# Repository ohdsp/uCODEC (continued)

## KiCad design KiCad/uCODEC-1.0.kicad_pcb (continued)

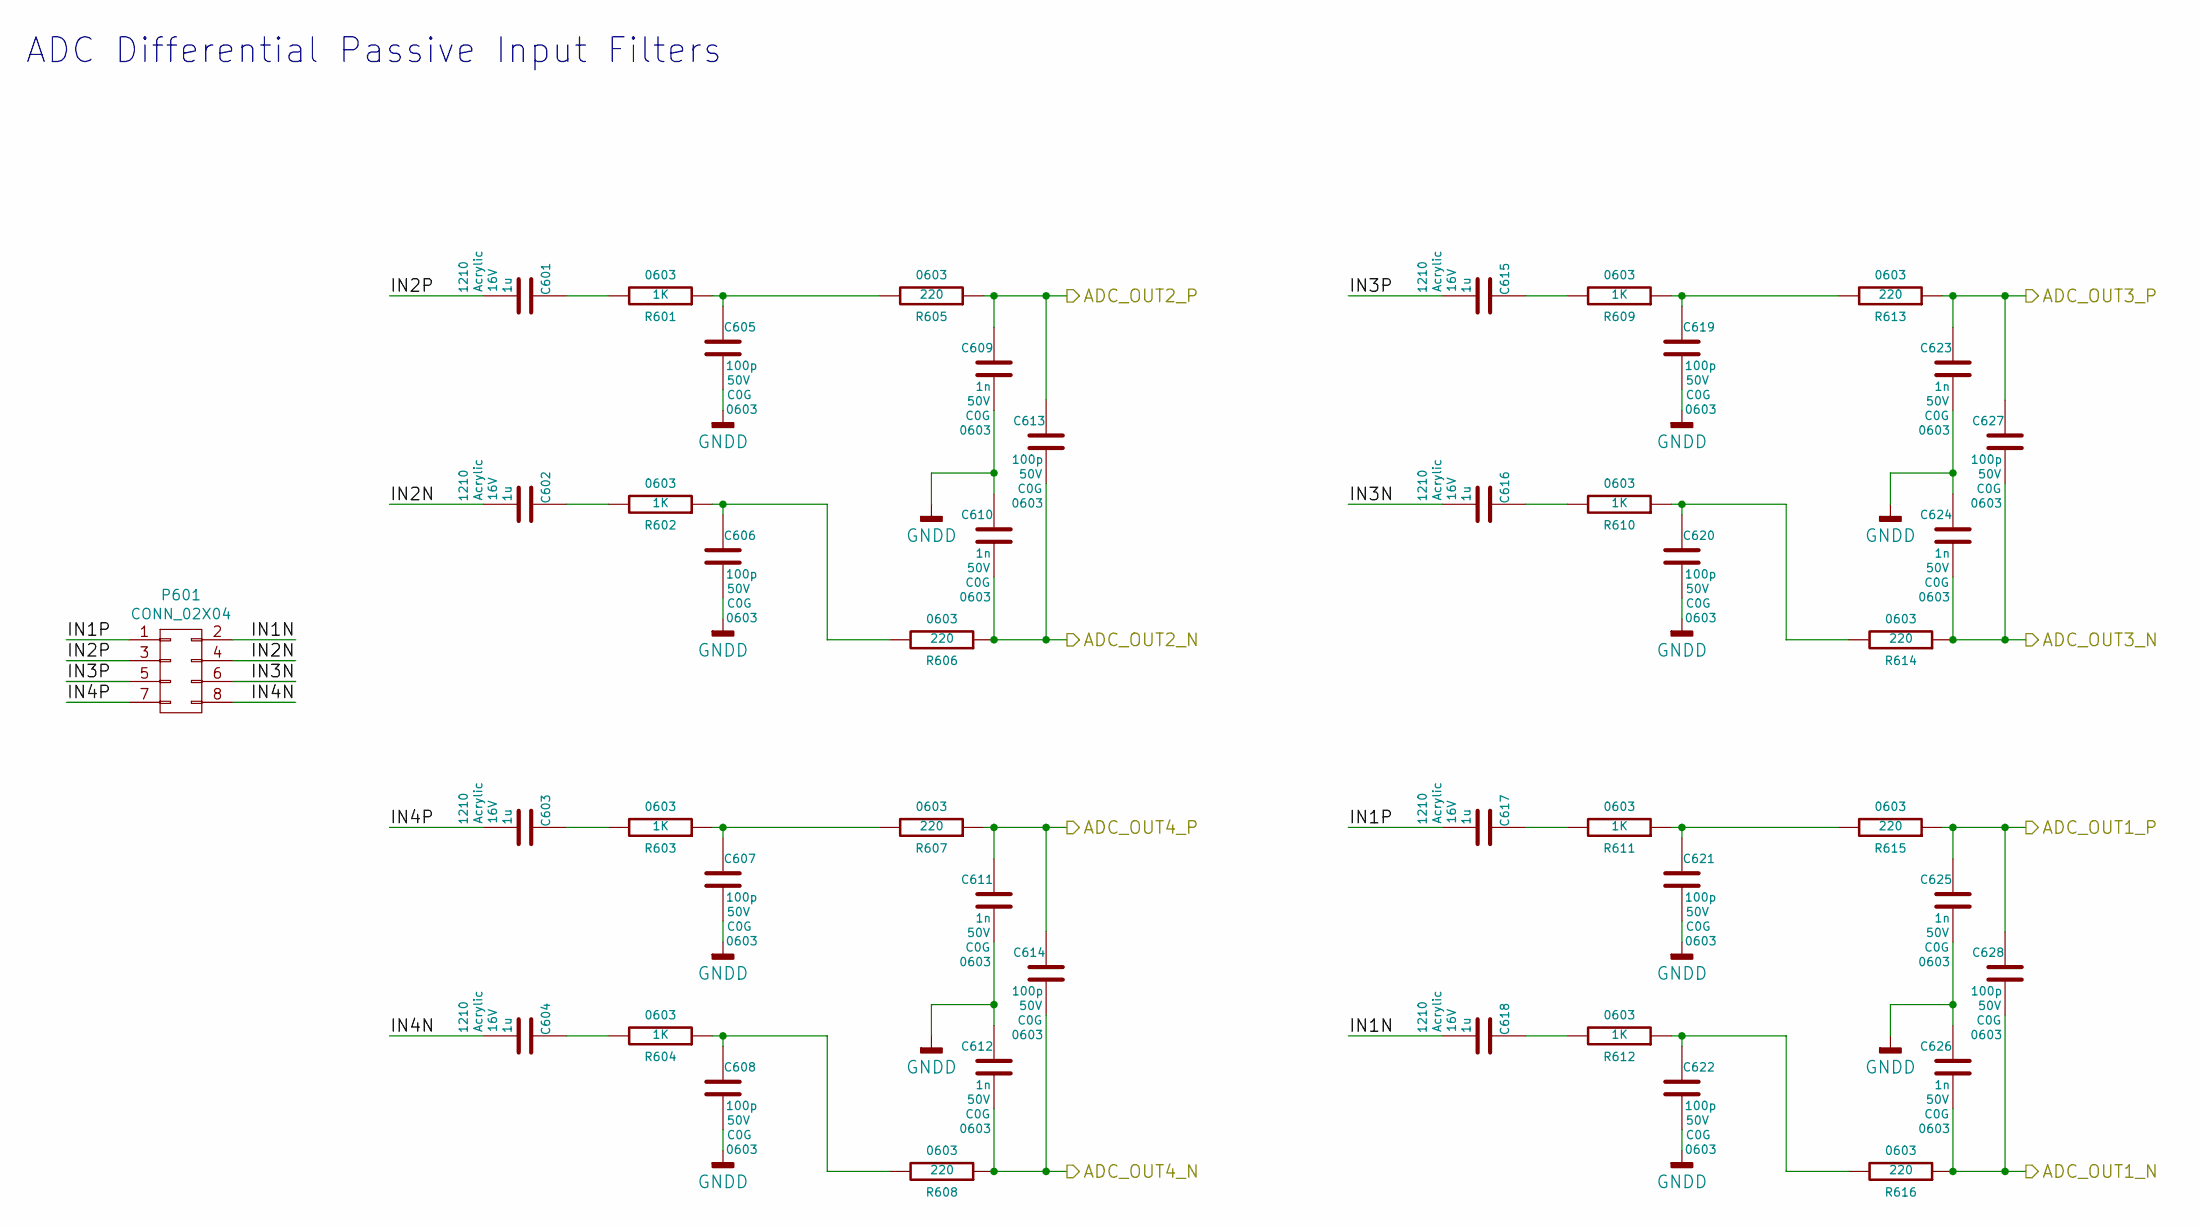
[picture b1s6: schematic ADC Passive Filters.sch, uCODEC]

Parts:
C601, C602, C604, C615, C616, C617, C618: 1u; SMD-1210; Voltage 16V; Tolerance 20%
C603, C607, C608, C609, C614, C619, C620, C621, C622, C627, C628: 100p; SMD-0603; Voltage 50V; Tolerance 5%
C605, C606, C611, C612, C623, C624, C625, C626: 1n; SMD-0603; Voltage 50V; Tolerance 5%
P601: CONN_02X04; CONN_DIL_2X04
R601, R602, R603, R604, R609, R610, R611, R612: 1K; SMD-0603; Tolerance 1%
R607, R608, R613, R614, R615, R616: 220; SMD-0603; Tolerance 1%

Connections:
/ADC2LN: C624.2, C627.2, R614.1; also elsewhere on the board
/ADC2LP: C623.1, C627.1, R613.1; also elsewhere on the board
/ADC2RN: C612.2, C614.2, R608.1; also elsewhere on the board
/ADC2RP: C611.1, C614.1, R607.1; also elsewhere on the board
/ADC Passive Filters/IN1N: C618.2, P601.2
/ADC Passive Filters/IN1P: C617.2, P601.1
/ADC Passive Filters/IN2N: C602.2, P601.4
/ADC Passive Filters/IN2P: C601.2, P601.3
/ADC Passive Filters/IN3N: C616.2, P601.6
/ADC Passive Filters/IN3P: C615.2, P601.5
/ADC Passive Filters/IN4N: C604.2, P601.8
unnamed: C601.1, R601.2
unnamed: C602.1, R602.2
unnamed: C604.1, R604.2
unnamed: C607.1, R603.1, R607.2
unnamed: C608.1, R604.1, R608.2
unnamed: C615.1, R609.2
unnamed: C616.1, R610.2
unnamed: C617.1, R611.2
unnamed: C618.1, R612.2
unnamed: C619.1, R609.1, R613.2
unnamed: C620.1, R610.1, R614.2

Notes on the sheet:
ADC Differential Passive Input Filters

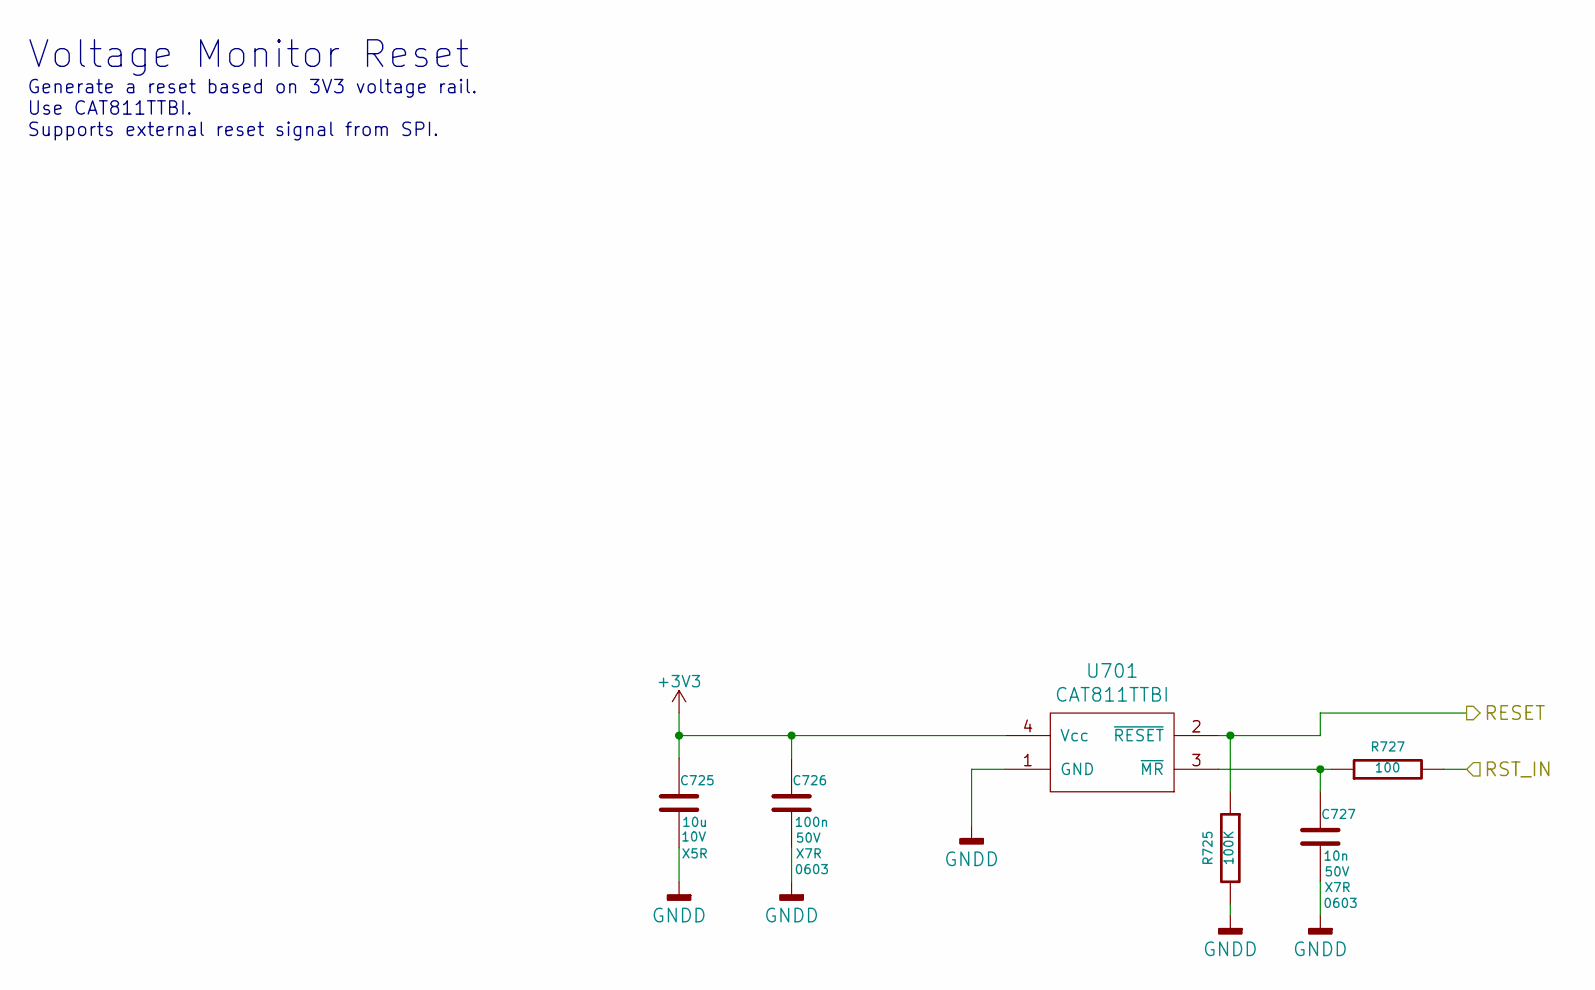
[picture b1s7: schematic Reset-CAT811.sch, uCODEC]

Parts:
C725: 10u; SMD-0603; Voltage 10V; Tolerance 20%
C726: 100n; SMD-0603; Voltage 50V; Tolerance 10%
C727: 10n; SMD-0603; Voltage 50V; Tolerance 10%
R725: 100K; SMD-0603; Tolerance 1%
R727: 100; SMD-0603; Tolerance 1%
U701: CAT811TTBI; IC-SOT143

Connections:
+3V3: C725.1, C726.1, U701.4 (Vcc); also elsewhere on the board
/CODEC_RST: R725.1, U701.2 (~RESET); also elsewhere on the board
/GLB_RESET: R727.2; also elsewhere on the board
unnamed: C727.1, R727.1, U701.3 (~MR)

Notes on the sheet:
Generate a reset based on 3V3 voltage rail. Use CAT811TTBI. Supports external reset signal from SPI.
Voltage Monitor Reset

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
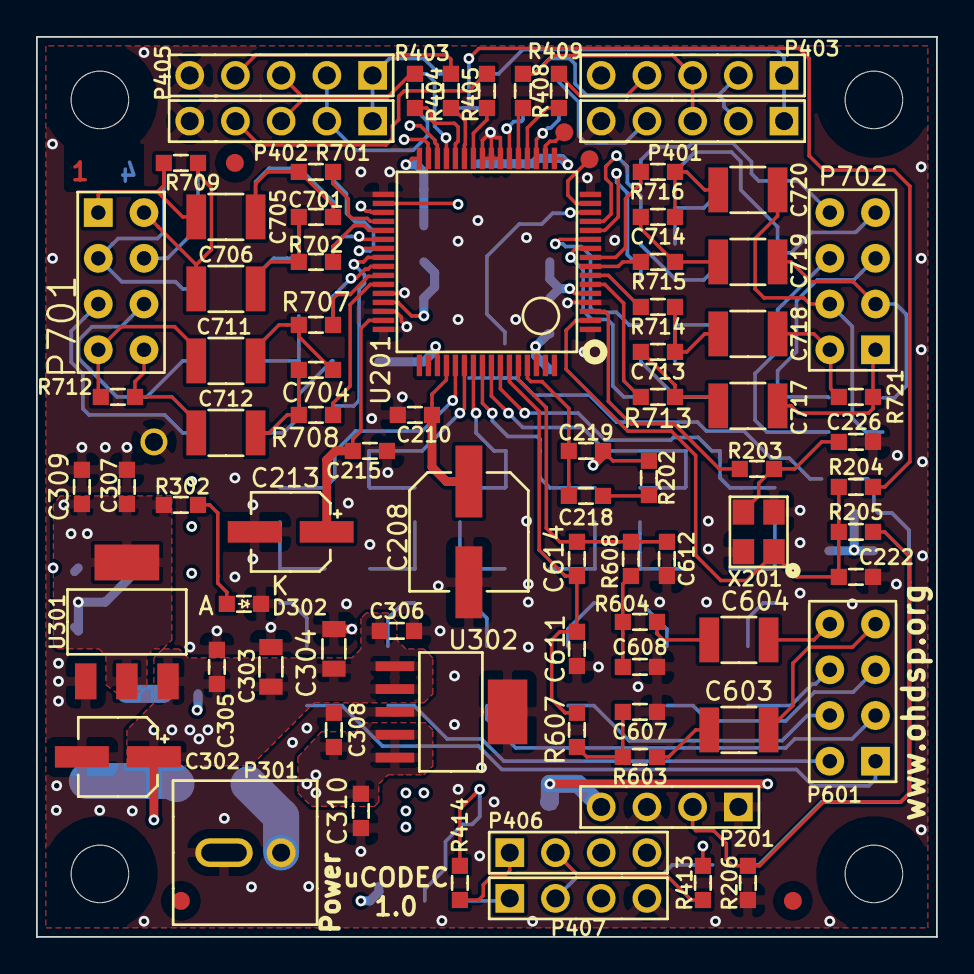
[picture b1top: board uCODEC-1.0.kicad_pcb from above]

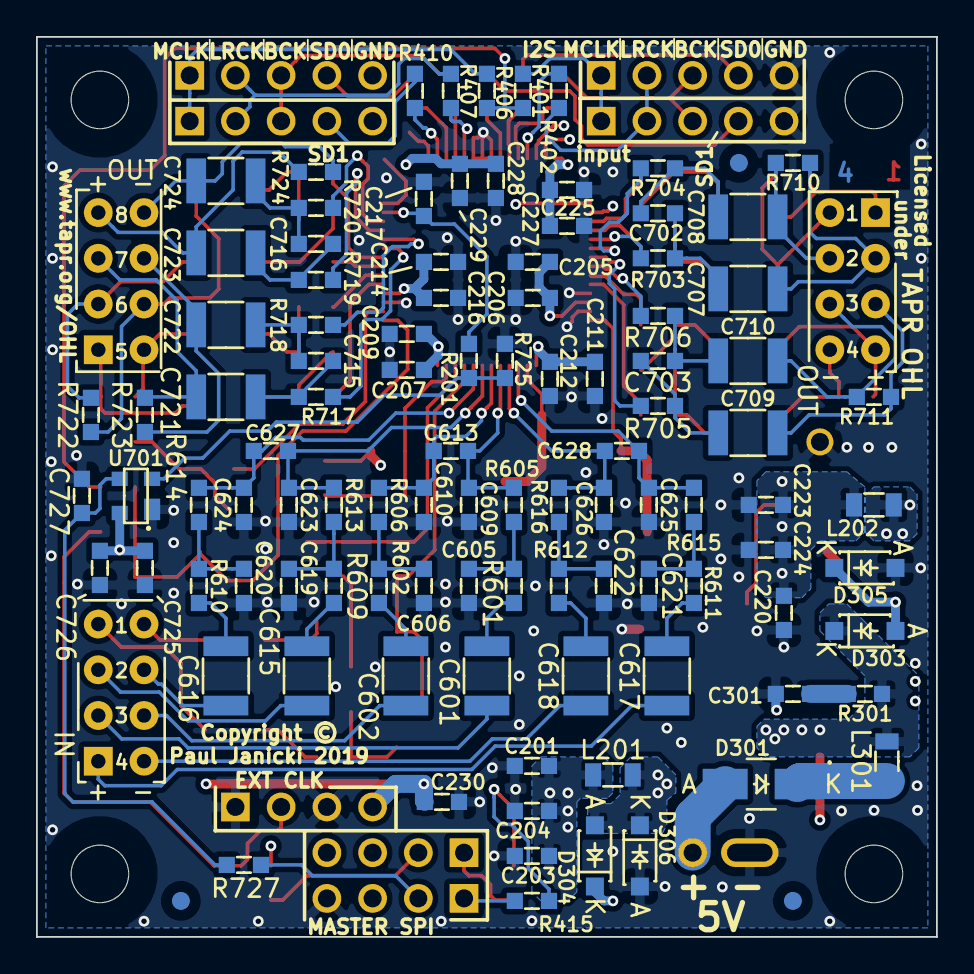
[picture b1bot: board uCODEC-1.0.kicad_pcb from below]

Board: 4 copper layers, 50.0 x 50.0 mm, 194 parts (104 on the bottom side), 130 nets.

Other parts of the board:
C610: 1n; SMD-0603
C613: 100p; SMD-0603
R605, R606: 220; SMD-0603

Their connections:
/ADC1RN: C610.2, C613.2, R606.1; also elsewhere on the board

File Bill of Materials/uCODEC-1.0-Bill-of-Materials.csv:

Reference; Quantity; Footprint; Value; Description; Size; Tolerance; Type; Voltage; Power; Current; 
C201 C220 C301 ;3;SMD-0603;100p;'Ceramic capacitor;'0603;'5%;'NP0;'50V;';';
C204 C205 C207 C210 C211 C214 C215 C224 C225 C228 C230 C305 C306 C307 C308 C726 ;16;SMD-0603;100n;'Ceramic capacitor;'0603;'10%;'X7R;'50V;';';
C206 C209 C212 C216 C217 C227 C229 C727 ;8;SMD-0603;10n;'Ceramic capacitor;'0603;'10%;'X7R;'50V;';';
C208 ;1;CAP-SMD-SIZE-D;47u;'Low impedance aluminium electrolytic capacitor - Panasonic FP, FK or Similar;';';'Case D SMD Aluminium Electrolytic;'16V;';';
C213 C302 ;2;CAP-SMD-SIZE-B;10u;'Low impedance aluminium electrolytic capacitor - Panasonic FP, FK or Similar;';';'Case B SMD Aluminium Electrolytic;'16V;';';
C218 ;1;SMD-0603;39n;'Ceramic capacitor;'0603;'10%;'X7R;'50V;';';
C219 ;1;SMD-0603;2n2;'Ceramic capacitor;'0603;'5%;'C0G;'50V;';';
C222 C226 ;2;SMD-0603;N/F;'Ceramic capacitor;'0603;'5%;'C0G;'25V;';';
C203 C223 C309 C310 ;4;SMD-0603;22u;'Ceramic capacitor;'0603;'20%;'X5R;'10V;';';
C303 C304 ;2;SMD-0805;22u;'Ceramic capacitor;'0805;'20%;'X5R;'25V;';';
C605 C606 C607 C608 C613 C614 C619 C620 C621 C622 C627 C628 ;12;SMD-0603;100p;'Ceramic capacitor;'0603;'5%;'C0G;'50V;';';
C609 C610 C611 C612 C623 C624 C625 C626 C701 C702 C703 C704 C713 C714 C715 C716 ;16;SMD-0603;1n;'Ceramic capacitor;'0603;'5%;'C0G;'50V;';';
C601 C602 C603 C604 C615 C616 C617 C618 C705 C706 C707 C708 C709 C710 C711 C712 C717 C718 C719 C720 C721 C722 C723 C724 ;24;SMD-1210;1u;'Acrylic capacitor;'1210;'20%;'Acrylic;'16V;';';
C725 ;1;SMD-0603;10u;'Ceramic capacitor;'0603;'20%;'X5R;'10V;';';
D301 ;1;DIODE-SMA;B240A;'B240A 2A 40V Schottky Rectifier - SMA (DO-214AC);';';';';';';
D302 ;1;SMD-0603-LED;LED 0603;'LED - SMD - Vf 1.8V to 2.2V;'0603;';';';';';
D303 D304 D305 D306 ;4;DIODE-SOD-123;1N5819HW;'1A 40V Schottky Rectifier - SOD-123;';';';';';';
FID301 FID302 FID303 FID304 FID305 FID306 ;6;FID-1MM-2MM;MNT_HOLE;'Fiducial;';';';';';';
L201 L202 L301 ;3;SMD-0805;600R@100MHz;'Ferrite bead, current rating 1A or higher, 600R@100MHz;'0805;';';';';'=>1A;
MNT301 MNT302 MNT303 MNT304 ;4;MNT_HOLE_3.2mm;MNT_HOLE;'Mounting hole;';';';';';';
P201 P406 P407 ;3;CONN_SIL_4_1MM;CONN_4x1;'Text description;';';';';';';
P301 ;1;CONN-2WAY-2.54mm-3.81mm-SPACING;CONN_2x1;'2 way screw terminal, any 2.54mm to 3.81mm pitch part;';';';';';';
P404 P408 ;2;TP-1mm;PIN;'Text description;';';';';';';
P401 P402 P403 P405 ;4;CONN_SIL_5_1MM;CONN_5x1;'Text description;';';';';';';
P601 P701 P702 ;3;CONN_DIL_2X04;CONN_02X04;'Text description;';';';';';';
R202 ;1;SMD-0603;3K32;'Thick or thin film resistor;'0603;'1%;';';'63mW;';
R203 R205 R206 R406 R414 ;5;SMD-0603;N/F;'Thick or thin film resistor;'0603;'1%;';';'63mW;';
R201 R204 R404 R405 R413 R415 ;6;SMD-0603;22;'Thick or thin film resistor;'0603;'1%;';';'63mW;';
R301 ;1;SMD-0603;47;'Thick or thin film resistor;'0603;'1%;';';'63mW;';
R302 ;1;SMD-0603;470;'Thick or thin film resistor;'0603;'1%;';';'63mW;';
R401 R402 R403 R407 R408 R409 R410 ;7;SMD-0603;0;'Thick or thin film resistor;'0603;'1%;';';'63mW;';
R605 R606 R607 R608 R613 R614 R615 R616 ;8;SMD-0603;220;'Thick or thin film resistor;'0603;'1%;';';'63mW;';
R601 R602 R603 R604 R609 R610 R611 R612 R701 R702 R703 R704 R705 R706 R707 R708 R713 R714 R715 R716 R717 R718 R719 R720 ;24;SMD-0603;1K;'Thick or thin film resistor;'0603;'1%;';';'63mW;';
R709 R710 R711 R712 R721 R722 R723 R724 ;8;SMD-0603;220K;'Thick or thin film resistor;'0603;'1%;';';'63mW;';
R725 ;1;SMD-0603;100K;'Thick or thin film resistor;'0603;'1%;';';'63mW;';
R727 ;1;SMD-0603;100;'Thick or thin film resistor;'0603;'1%;';';'63mW;';
TP401 ;1;TP-TH-1mm;PIN;
U201 ;1;IC-LQFP64;AD1939;'Analog Devices AD1939WBSTZ - 4 ADC/8 DAC with PLL;';';';';';';
U301 ;1;IC-SOT-223;TLV1117LV33DCY;'TLV1117LV 1-A, Positive Fixed-Voltage, Low-Dropout Regulator - Fixed 3V3;';';';';';';
U302 ;1;IC-SOT223-6;TPS7A4533DCQ;'TI TPS7A45xx Regulator;';';';';';';
U701 ;1;IC-SOT143;CAT811TTBI;'CAT811/ADM811 - 4-Pin Microprocessor Power Supply Supervisor with Manual Reset - Active Low;';';';';';';
X201 ;1;XTAL_3.2x2.5_4PIN;N/F;'Not Fitted - 3.2x2.5mm crystal;';';';';';';

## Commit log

2019-04-02 uCODEC 1.0
    uCODEC 1.0
